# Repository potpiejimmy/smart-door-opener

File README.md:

# smart-door-opener
Opening a building's door via Arduino compatible relay module and Alexa skill

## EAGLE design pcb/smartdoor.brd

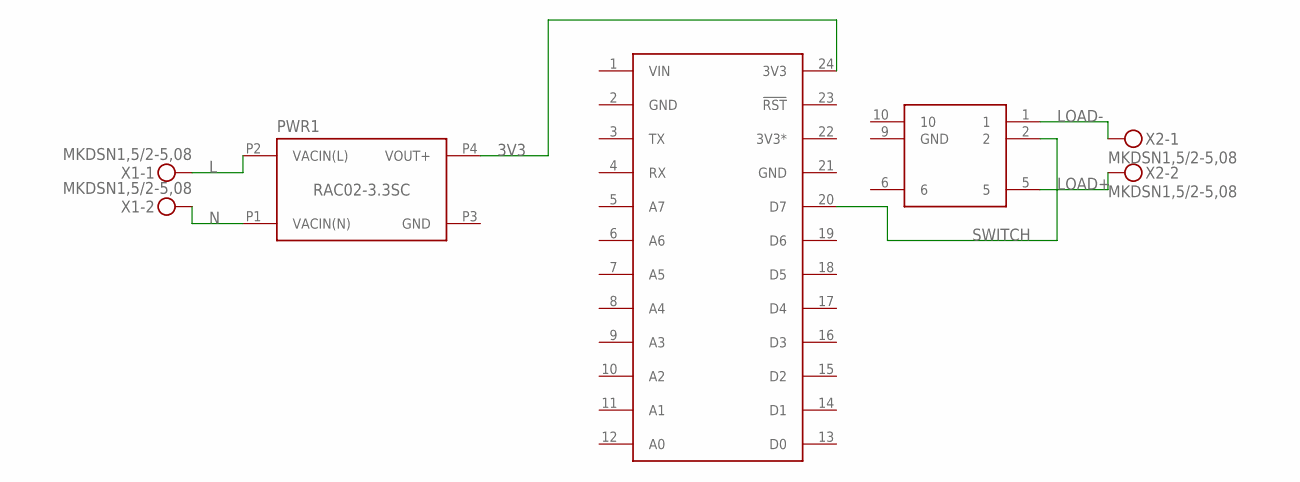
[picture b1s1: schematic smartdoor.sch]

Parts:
CORE: SPARK_CORECORE; SPARK_CORE
PWR1: RAC02-3.3SC; LOW_PROFILE_POWER_MODULE
RELAY1: AZ9571AZ9571; AZ9571
X1, X2: MKDSN1,5/2-5,08

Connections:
3V3: CORE.24 (3V3), PWR1.P4 (VOUT+)
3V3*: CORE.22 (3V3*)
GND: CORE.2 (GND), CORE.21 (GND), PWR1.P3 (GND), RELAY1.9 (GND)
L: PWR1.P2 (VACIN(L)), X1.1
LOAD+: RELAY1.5, X2.2
LOAD-: RELAY1.1, X2.1
N: PWR1.P1 (VACIN(N)), X1.2
SWITCH: CORE.20 (D7), RELAY1.2
VIN: CORE.1 (VIN)

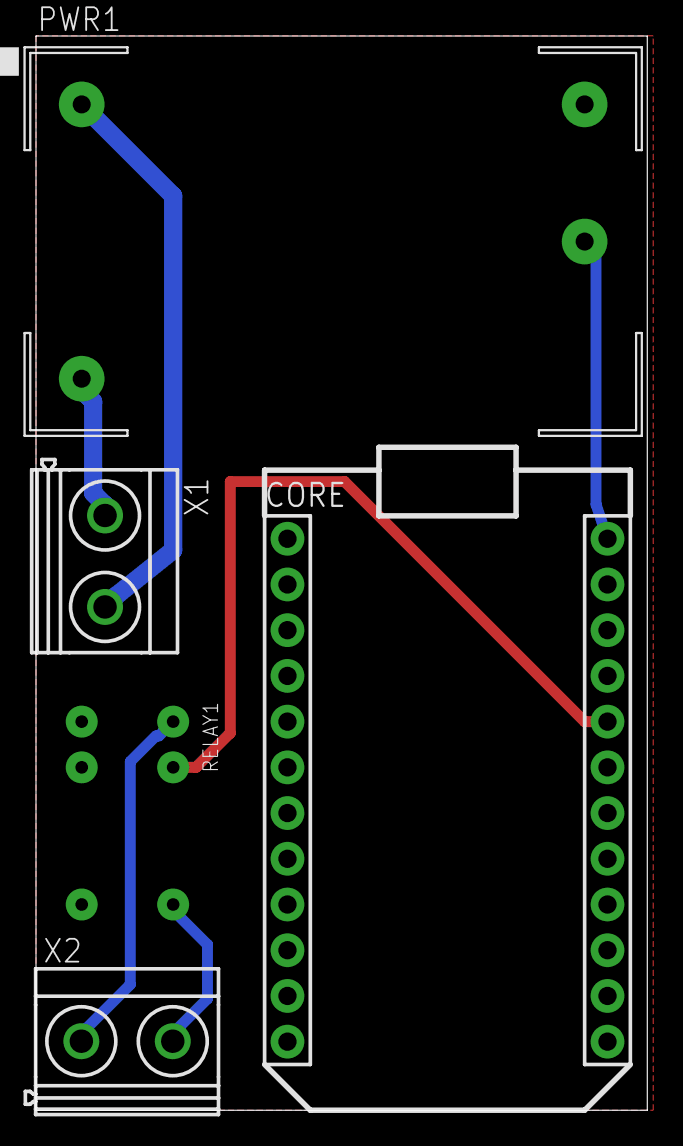
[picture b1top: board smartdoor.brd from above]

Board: 2 copper layers, 34.0 x 59.7 mm, 5 parts (0 on the bottom side), 7 nets.

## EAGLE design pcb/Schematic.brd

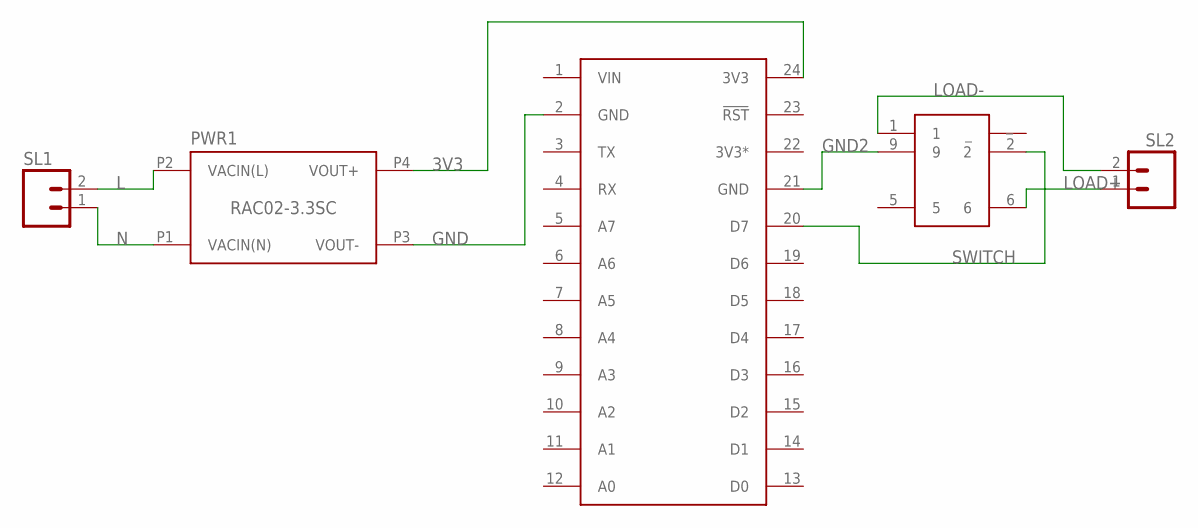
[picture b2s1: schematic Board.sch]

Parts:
CORE: SPARK_CORECORE; SPARK_CORE
PWR1: RAC02-3.3SC; LOW_PROFILE_POWER_MODULE
RELAY1: AZ9571AZ9571; AZ9571
SL1, SL2: M02; 02P

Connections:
3V3: CORE.24 (3V3), PWR1.P4 (VOUT+)
3V3*: CORE.22 (3V3*)
GND: CORE.2 (GND), PWR1.P3 (VOUT-)
GND2: CORE.21 (GND), RELAY1.9
L: PWR1.P2 (VACIN(L)), SL1.2
LOAD+: RELAY1.6, SL2.1
LOAD-: RELAY1.1, SL2.2
N: PWR1.P1 (VACIN(N)), SL1.1
SWITCH: CORE.20 (D7), RELAY1.2
VIN: CORE.1 (VIN)

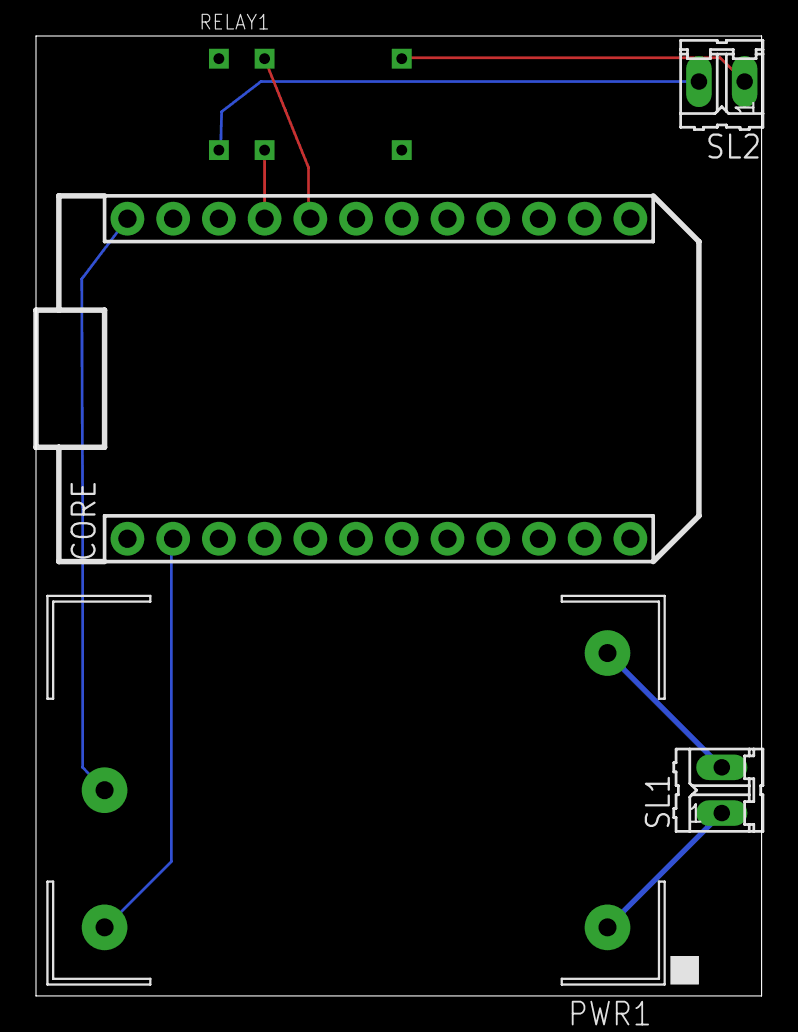
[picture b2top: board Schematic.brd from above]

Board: 2 copper layers, 40.3 x 53.3 mm, 5 parts (0 on the bottom side), 8 nets.

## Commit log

2017-05-17 eagle PCB schematic and board
2017-05-18 board layout changes
2017-05-19 new pcb board layout, renamed files
2017-05-20 defined net classes and GND pins on relay, new board layout
2017-05-21 final board with two net classes, ground fills and non-via routings
2017-05-22 larger copper pad for zettler relay
2017-05-22 fixed connecting V- of recom with GND mass, updated larger pads for zettler relay in board
2017-05-22 added rendered board images
2017-05-23 fixed mirrored relay
2017-06-03 implemented particle code and lambda function
2017-06-04 fixed post request
2017-06-04 perform async buzz on core
